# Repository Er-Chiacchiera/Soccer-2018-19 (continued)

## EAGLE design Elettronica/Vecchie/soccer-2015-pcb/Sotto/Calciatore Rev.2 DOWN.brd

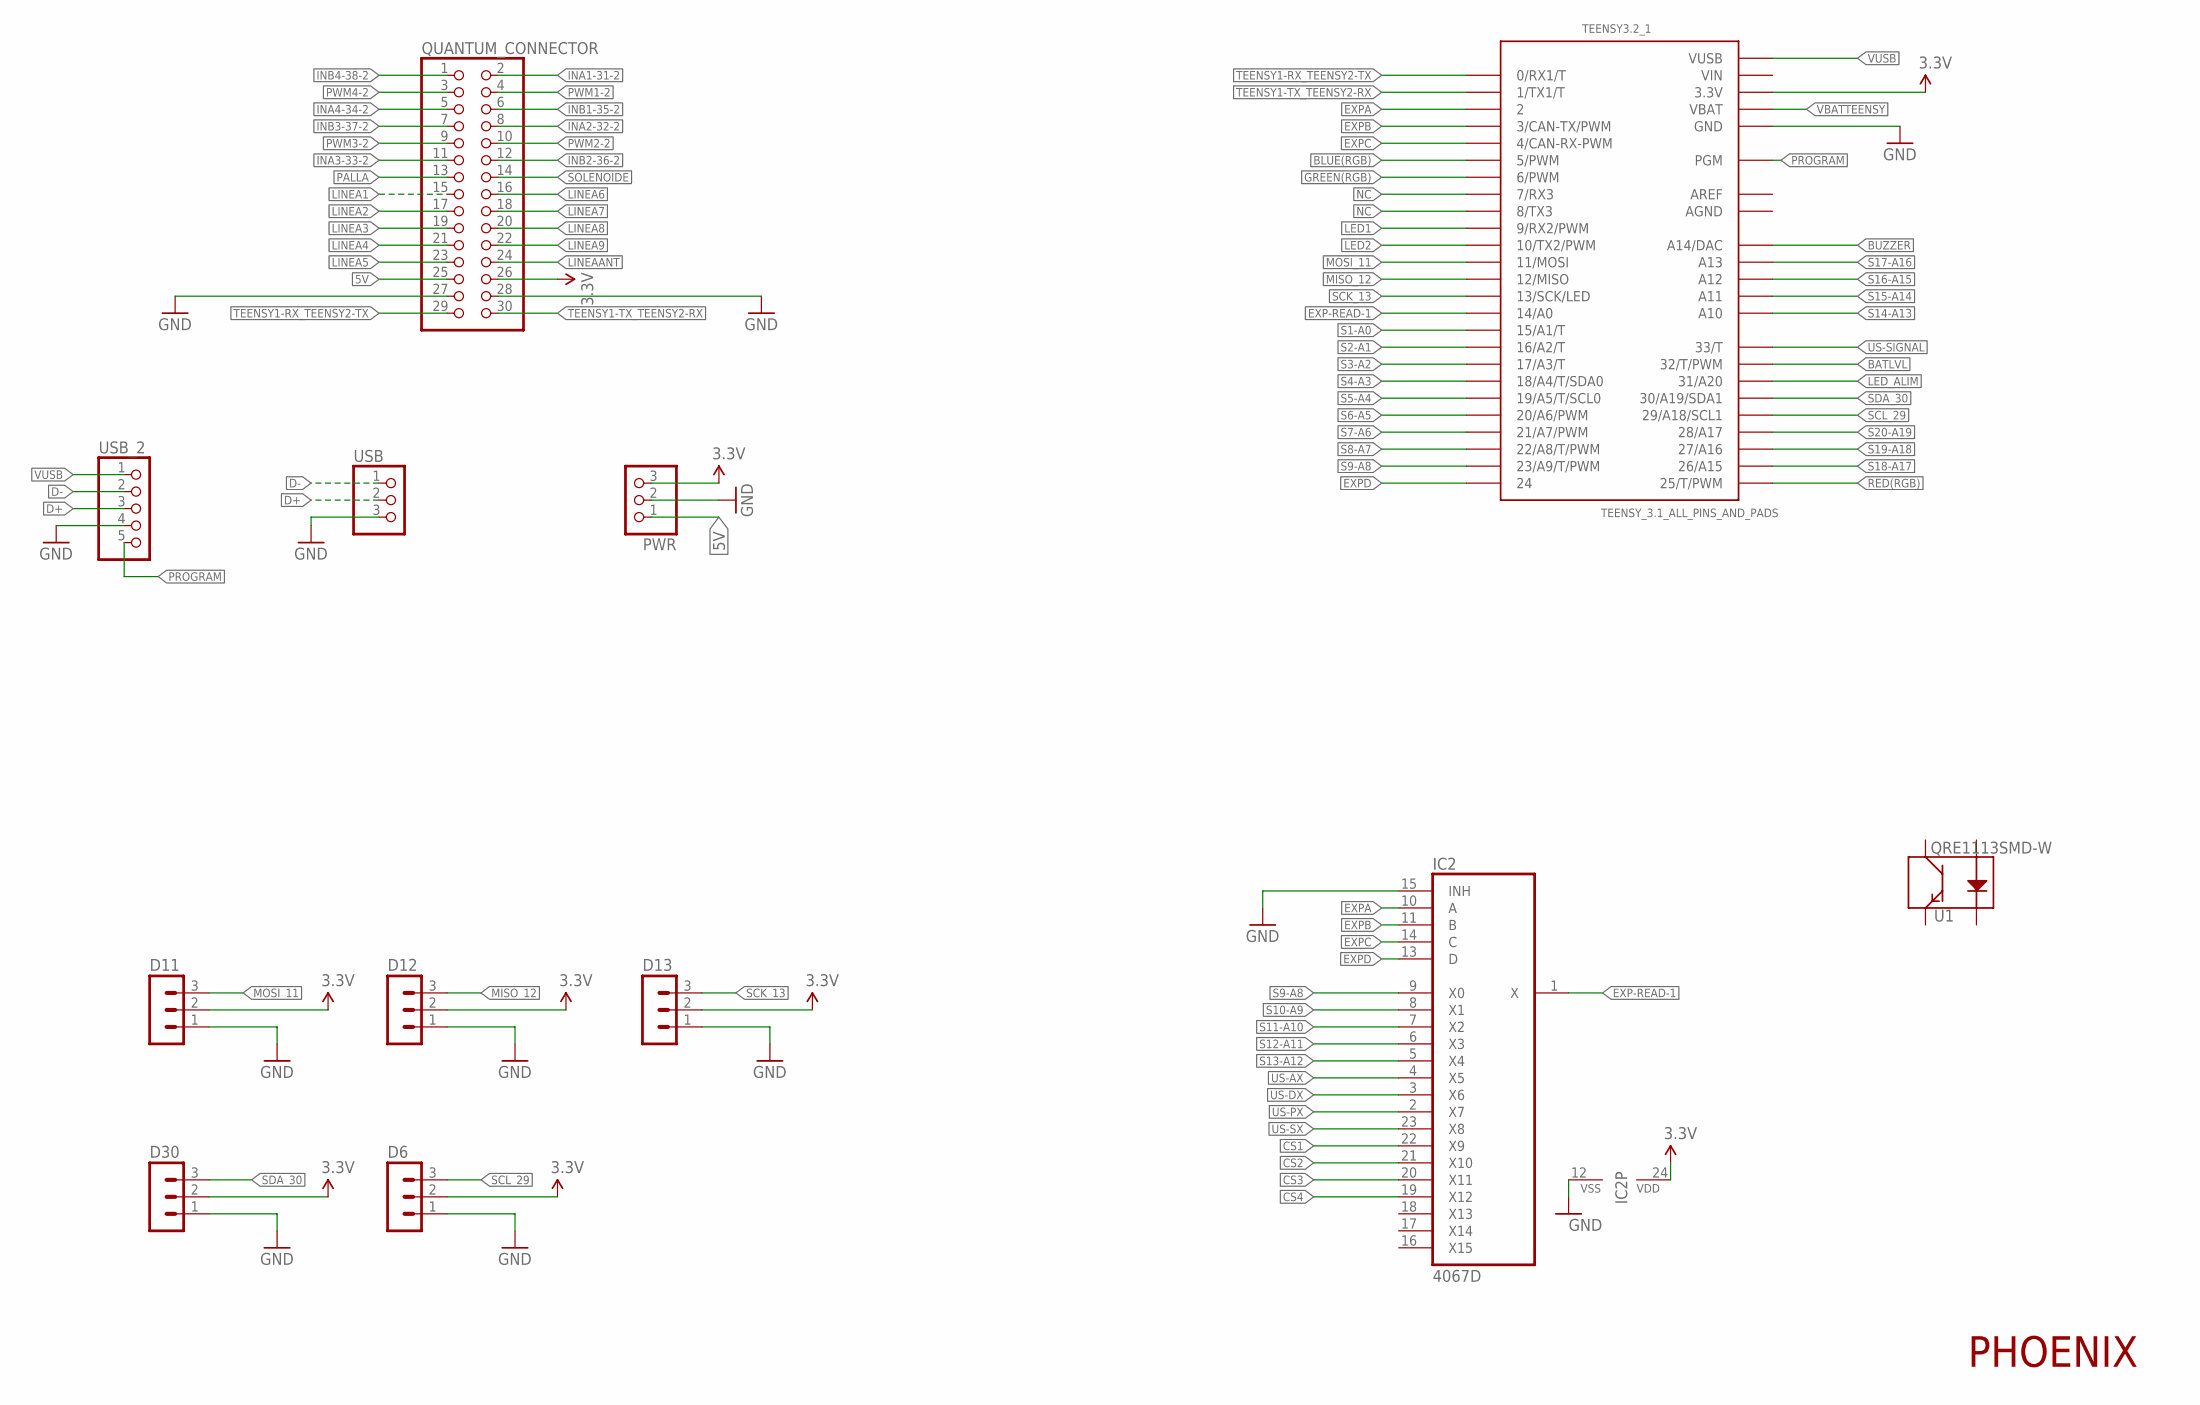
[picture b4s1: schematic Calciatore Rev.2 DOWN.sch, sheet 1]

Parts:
D6, D11, D12, D13, D30: MA03-1
IC2: 4067D; SO24W
PWR: PINHD-1X3; 1X03
QUANTUM_CONNECTOR: PINHD-2X15; 2X15
TEENSY3.2_1: TEENSY_3.1_ALL_PINS_AND_PADS; TEENSY3_ALL_PINS_&_PADS
U1: QRE1113SMD-W; QRE1113-W
USB: PINHD-1X3; 1X03
USB_2: PINHD-1X5; 1X05

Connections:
3.3V: D6.2, D11.2, D12.2, D13.2, D30.2, IC2.24 (VDD), PWR.3, QUANTUM_CONNECTOR.26, TEENSY3.2_1.3.3V, TEENSY3.2_1.3.3V1 (3.3V), TEENSY3.2_1.3.3V2 (3.3V); also elsewhere on the board
5V: PWR.1, QUANTUM_CONNECTOR.25; also elsewhere on the board
AGND: TEENSY3.2_1.AGND
AREF: TEENSY3.2_1.AREF
BATLVL: TEENSY3.2_1.32 (32/T/PWM); also elsewhere on the board
BLUE(RGB): TEENSY3.2_1.5 (5/PWM); also elsewhere on the board
BUZZER: TEENSY3.2_1.RESET/DAC (A14/DAC); also elsewhere on the board
CS1: IC2.22 (X9); also elsewhere on the board
CS2: IC2.21 (X10); also elsewhere on the board
CS3: IC2.20 (X11); also elsewhere on the board
CS4: IC2.19 (X12); also elsewhere on the board
D+: USB.2, USB_2.3
D-: USB.1, USB_2.2
EXP-READ-1: IC2.1 (X), TEENSY3.2_1.14/A0
EXPA: IC2.10 (A), TEENSY3.2_1.2
EXPB: IC2.11 (B), TEENSY3.2_1.3 (3/CAN-TX/PWM)
EXPC: IC2.14 (C), TEENSY3.2_1.4 (4/CAN-RX-PWM)
EXPD: IC2.13 (D), TEENSY3.2_1.24
GND: D6.1, D11.1, D12.1, D13.1, D30.1, IC2.12 (VSS), IC2.15 (INH), PWR.2, QUANTUM_CONNECTOR.27, QUANTUM_CONNECTOR.28, TEENSY3.2_1.GND, TEENSY3.2_1.GND1 (GND), TEENSY3.2_1.GND2 (GND), USB.3, USB_2.4; also elsewhere on the board
GREEN(RGB): TEENSY3.2_1.6 (6/PWM); also elsewhere on the board
INA1-31-2: QUANTUM_CONNECTOR.2; also elsewhere on the board
INA2-32-2: QUANTUM_CONNECTOR.8; also elsewhere on the board
INA3-33-2: QUANTUM_CONNECTOR.11; also elsewhere on the board
INA4-34-2: QUANTUM_CONNECTOR.5; also elsewhere on the board
INB1-35-2: QUANTUM_CONNECTOR.6; also elsewhere on the board
INB2-36-2: QUANTUM_CONNECTOR.12; also elsewhere on the board
INB3-37-2: QUANTUM_CONNECTOR.7; also elsewhere on the board
INB4-38-2: QUANTUM_CONNECTOR.1; also elsewhere on the board
LED1: TEENSY3.2_1.9 (9/RX2/PWM); also elsewhere on the board
LED2: TEENSY3.2_1.10 (10/TX2/PWM); also elsewhere on the board
LED_ALIM: TEENSY3.2_1.31 (31/A20); also elsewhere on the board
LINEA1: QUANTUM_CONNECTOR.15
LINEA2: QUANTUM_CONNECTOR.17
LINEA3: QUANTUM_CONNECTOR.19
LINEA4: QUANTUM_CONNECTOR.21
LINEA5: QUANTUM_CONNECTOR.23
LINEA6: QUANTUM_CONNECTOR.16
LINEA7: QUANTUM_CONNECTOR.18
LINEA8: QUANTUM_CONNECTOR.20
LINEA9: QUANTUM_CONNECTOR.22
LINEAANT: QUANTUM_CONNECTOR.24
MISO_12: D12.3, TEENSY3.2_1.12 (12/MISO)
MOSI_11: D11.3, TEENSY3.2_1.11 (11/MOSI)
NC: TEENSY3.2_1.7 (7/RX3), TEENSY3.2_1.8 (8/TX3)
PALLA: QUANTUM_CONNECTOR.13
PROGRAM: TEENSY3.2_1.PGM, USB_2.5
PWM1-2: QUANTUM_CONNECTOR.4; also elsewhere on the board
PWM2-2: QUANTUM_CONNECTOR.10; also elsewhere on the board
PWM3-2: QUANTUM_CONNECTOR.9; also elsewhere on the board
PWM4-2: QUANTUM_CONNECTOR.3; also elsewhere on the board
RED(RGB): TEENSY3.2_1.25 (25/T/PWM); also elsewhere on the board
S1-A0: TEENSY3.2_1.15/A1 (15/A1/T); also elsewhere on the board
S2-A1: TEENSY3.2_1.16/A2 (16/A2/T); also elsewhere on the board
S3-A2: TEENSY3.2_1.17/A3 (17/A3/T); also elsewhere on the board
S4-A3: TEENSY3.2_1.18/A4 (18/A4/T/SDA0); also elsewhere on the board
S5-A4: TEENSY3.2_1.19/A5 (19/A5/T/SCL0); also elsewhere on the board
S6-A5: TEENSY3.2_1.20/A6 (20/A6/PWM); also elsewhere on the board
S7-A6: TEENSY3.2_1.21/A7 (21/A7/PWM); also elsewhere on the board
S8-A7: TEENSY3.2_1.22/A8 (22/A8/T/PWM); also elsewhere on the board
S9-A8: IC2.9 (X0), TEENSY3.2_1.23/A9 (23/A9/T/PWM); also elsewhere on the board
S10-A9: IC2.8 (X1); also elsewhere on the board
S11-A10: IC2.7 (X2); also elsewhere on the board
S12-A11: IC2.6 (X3); also elsewhere on the board
S13-A12: IC2.5 (X4); also elsewhere on the board
S14-A13: TEENSY3.2_1.A10; also elsewhere on the board
S15-A14: TEENSY3.2_1.A11; also elsewhere on the board
S16-A15: TEENSY3.2_1.A12; also elsewhere on the board
S17-A16: TEENSY3.2_1.A13; also elsewhere on the board
S18-A17: TEENSY3.2_1.26 (26/A15); also elsewhere on the board
S19-A18: TEENSY3.2_1.27 (27/A16); also elsewhere on the board
S20-A19: TEENSY3.2_1.28 (28/A17); also elsewhere on the board
SCK_13: D13.3, TEENSY3.2_1.13 (13/SCK/LED)
SCL_29: D6.3, TEENSY3.2_1.29 (29/A18/SCL1)
SDA_30: D30.3, TEENSY3.2_1.30 (30/A19/SDA1)
SOLENOIDE: QUANTUM_CONNECTOR.14; also elsewhere on the board
TEENSY1-RX_TEENSY2-TX: QUANTUM_CONNECTOR.29, TEENSY3.2_1.0 (0/RX1/T)
TEENSY1-TX_TEENSY2-RX: QUANTUM_CONNECTOR.30, TEENSY3.2_1.1 (1/TX1/T)
US-AX: IC2.4 (X5); also elsewhere on the board
US-DX: IC2.3 (X6); also elsewhere on the board
US-PX: IC2.2 (X7); also elsewhere on the board
US-SIGNAL: TEENSY3.2_1.33 (33/T); also elsewhere on the board
US-SX: IC2.23 (X8); also elsewhere on the board
VBATTEENSY: TEENSY3.2_1.VBAT
VIN: TEENSY3.2_1.VIN; also elsewhere on the board
VUSB: TEENSY3.2_1.VUSB, USB_2.1

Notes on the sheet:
PHOENIX

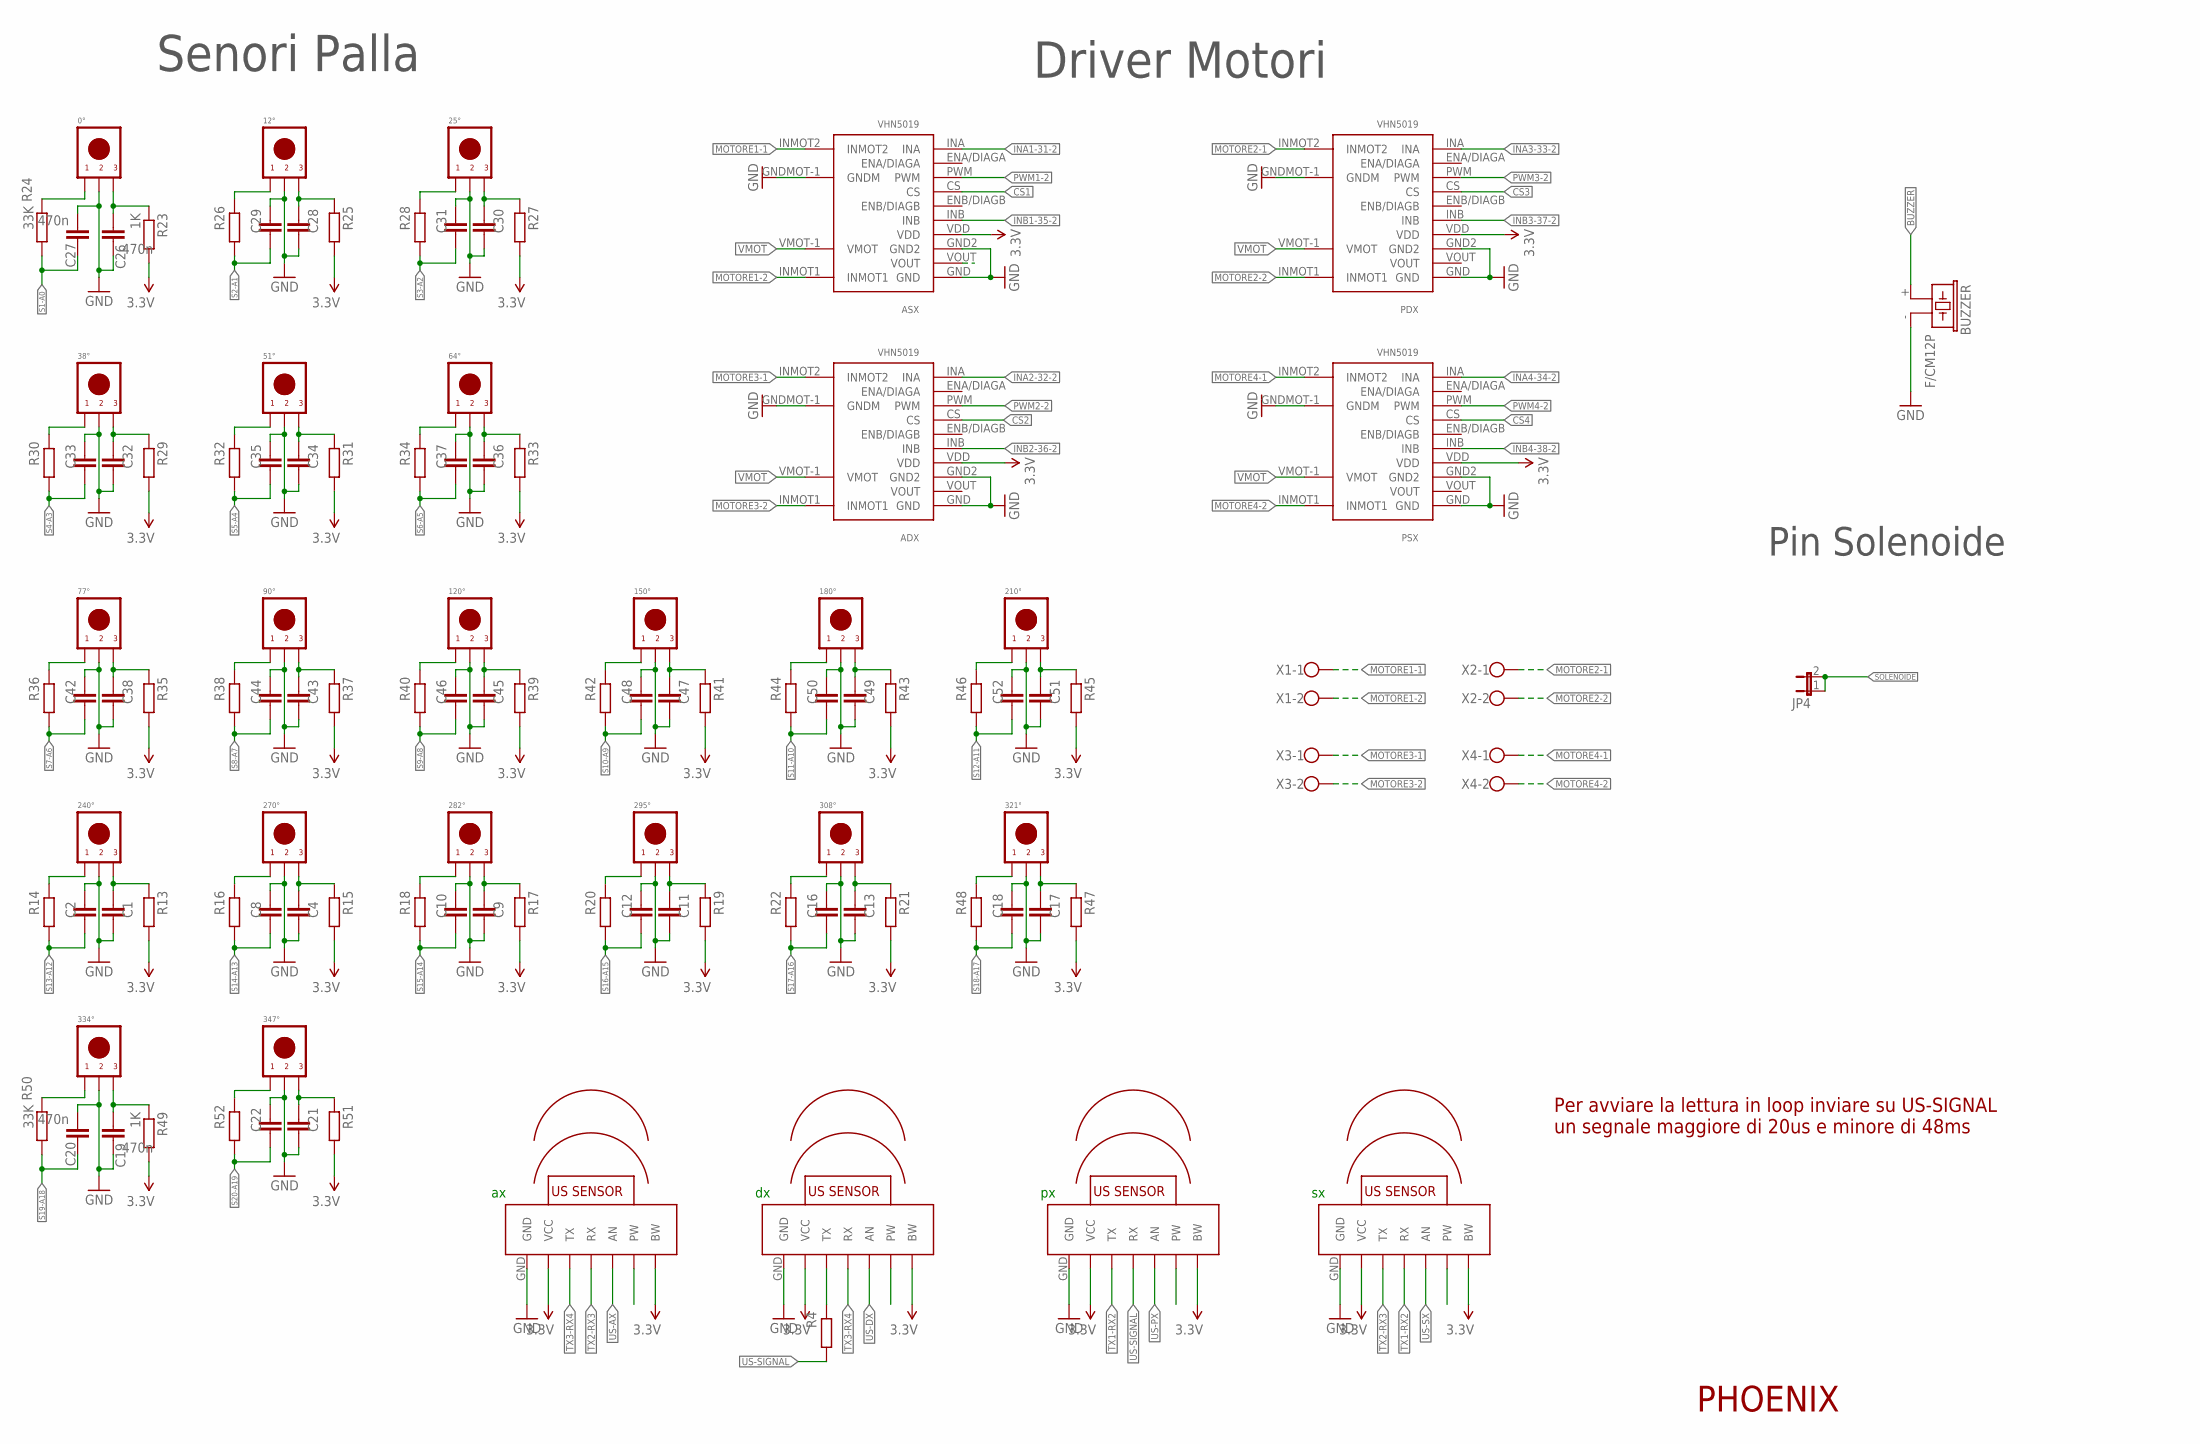
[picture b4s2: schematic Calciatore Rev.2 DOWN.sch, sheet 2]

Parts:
0°, 12°, 25°, 38°, 51°, 64°, 77°, 90°, 120°, 150°, 180°, 210°, 240°, 270°, 282°, 295°, 308°, 321°, 334°, 347°: effe; TSOP4840
ADX: VHN5019; MOTOR-SHIELD
ASX: VHN5019; MOTOR-SHIELD
AX: MB1010
BUZZER: F/CM12P
C1, C2, C4, C8, C9, C10, C11, C12, C13, C16, C17, C18, C21, C22, C28, C29, C30, C31, C32, C33, C34, C35, C36, C37, C38, C42, C43, C44, C45, C46, C47, C48, C49, C50, C51, C52: C-EUC1206; C1206
C19, C20, C26, C27: 470n; C1206
DX: MB1010
JP4: JP1E; JP1
PDX: VHN5019; MOTOR-SHIELD
PSX: VHN5019; MOTOR-SHIELD
PX: MB1010
R4, R13, R14, R15, R16, R17, R18, R19, R20, R21, R22, R25, R26, R27, R28, R29, R30, R31, R32, R33, R34, R35, R36, R37, R38, R39, R40, R41, R42, R43, R44, R45, R46, R47, R48, R51, R52: R-EU_M1206; M1206
R23, R49: 1K; M1206
R24, R50: 33K; M1206
SX: MB1010
X1, X2, X3, X4: W237-102

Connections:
3.3V: ADX.VDD, ASX.VDD, AX.BW, AX.VCC, DX.BW, DX.VCC, PDX.VDD, PSX.VDD, PX.BW, PX.VCC, R13.2, R15.2, R17.2, R19.2, R21.2, R23.2, R25.2, R27.2, R29.2, R31.2, R33.2, R35.2, R37.2, R39.2, R41.2, R43.2, R45.2, R47.2, R49.2, R51.2, SX.BW, SX.VCC; also elsewhere on the board
BUZZER: BUZZER.+ (1); also elsewhere on the board
CS1: ASX.CS; also elsewhere on the board
CS2: ADX.CS; also elsewhere on the board
CS3: PDX.CS; also elsewhere on the board
CS4: PSX.CS; also elsewhere on the board
GND: 0°.GND, 12°.GND, 25°.GND, 38°.GND, 51°.GND, 64°.GND, 77°.GND, 90°.GND, 120°.GND, 150°.GND, 180°.GND, 210°.GND, 240°.GND, 270°.GND, 282°.GND, 295°.GND, 308°.GND, 321°.GND, 334°.GND, 347°.GND, ADX.GND, ADX.GND2, ADX.GNDMOT-1 (GNDM), ASX.GND, ASX.GND2, ASX.GNDMOT-1 (GNDM), AX.GND, BUZZER.- (2), C1.2, C2.1, C4.2, C8.1, C9.2, C10.1, C11.2, C12.1, C13.2, C16.1, C17.2, C18.1, C19.2, C20.2, C21.2, C22.1, C26.2, C27.2, C28.2, C29.1, C30.2, C31.1, C32.2, C33.1, C34.2, C35.1, C36.2, C37.1, C38.2, C42.1, C43.2, C44.1, C45.2, C46.1, C47.2, C48.1, C49.2, C50.1, C51.2, C52.1, DX.GND, PDX.GND, PDX.GND2, PDX.GNDMOT-1 (GNDM), PSX.GND, PSX.GND2, PSX.GNDMOT-1 (GNDM), PX.GND, SX.GND; also elsewhere on the board
INA1-31-2: ASX.INA; also elsewhere on the board
INA2-32-2: ADX.INA; also elsewhere on the board
INA3-33-2: PDX.INA; also elsewhere on the board
INA4-34-2: PSX.INA; also elsewhere on the board
INB1-35-2: ASX.INB; also elsewhere on the board
INB2-36-2: ADX.INB; also elsewhere on the board
INB3-37-2: PDX.INB; also elsewhere on the board
INB4-38-2: PSX.INB; also elsewhere on the board
MOTORE1-1: ASX.INMOT2, X1.1
MOTORE1-2: ASX.INMOT1, X1.2
MOTORE2-1: PDX.INMOT2, X2.1
MOTORE2-2: PDX.INMOT1, X2.2
MOTORE3-1: ADX.INMOT2, X3.1
MOTORE3-2: ADX.INMOT1, X3.2
MOTORE4-1: PSX.INMOT2, X4.1
MOTORE4-2: PSX.INMOT1, X4.2
unnamed: 0°.VCC, C26.1, R23.1
unnamed: 0°.OUT, R24.1
unnamed: 12°.VCC, C28.1, R25.1
unnamed: 12°.OUT, R26.1
unnamed: 240°.VCC, C1.1, R13.1
unnamed: 270°.VCC, C4.1, R15.1
unnamed: 282°.VCC, C9.1, R17.1
unnamed: 25°.OUT, R28.1
unnamed: 38°.OUT, R30.1
unnamed: 51°.OUT, R32.1
unnamed: 25°.VCC, C30.1, R27.1
unnamed: 295°.VCC, C11.1, R19.1
unnamed: 308°.VCC, C13.1, R21.1
unnamed: 321°.VCC, C17.1, R47.1
unnamed: 64°.OUT, R34.1
unnamed: 38°.VCC, C32.1, R29.1
unnamed: 77°.OUT, R36.1
unnamed: 51°.VCC, C34.1, R31.1
unnamed: 120°.OUT, R40.1
unnamed: 64°.VCC, C36.1, R33.1
unnamed: 180°.OUT, R44.1
unnamed: 77°.VCC, C38.1, R35.1
unnamed: 90°.OUT, R38.1
unnamed: 90°.VCC, C43.1, R37.1
unnamed: 150°.OUT, R42.1
unnamed: 120°.VCC, C45.1, R39.1
unnamed: 210°.OUT, R46.1
unnamed: 150°.VCC, C47.1, R41.1
unnamed: 240°.OUT, R14.1
unnamed: 180°.VCC, C49.1, R43.1
unnamed: 270°.OUT, R16.1
unnamed: 210°.VCC, C51.1, R45.1
unnamed: 282°.OUT, R18.1
unnamed: 295°.OUT, R20.1
unnamed: 308°.OUT, R22.1
unnamed: 321°.OUT, R48.1
unnamed: 334°.VCC, C19.1, R49.1
unnamed: 347°.VCC, C21.1, R51.1
unnamed: 334°.OUT, R50.1
unnamed: 347°.OUT, R52.1
unnamed: DX.TX, R4.1
PWM1-2: ASX.PWM; also elsewhere on the board
PWM2-2: ADX.PWM; also elsewhere on the board
PWM3-2: PDX.PWM; also elsewhere on the board
PWM4-2: PSX.PWM; also elsewhere on the board
S1-A0: C27.1, R24.2; also elsewhere on the board
S2-A1: C29.2, R26.2; also elsewhere on the board
S3-A2: C31.2, R28.2; also elsewhere on the board
S4-A3: C33.2, R30.2; also elsewhere on the board
S5-A4: C35.2, R32.2; also elsewhere on the board
S6-A5: C37.2, R34.2; also elsewhere on the board
S7-A6: C42.2, R36.2; also elsewhere on the board
S8-A7: C44.2, R38.2; also elsewhere on the board
S9-A8: C46.2, R40.2; also elsewhere on the board
S10-A9: C48.2, R42.2; also elsewhere on the board
S11-A10: C50.2, R44.2; also elsewhere on the board
S12-A11: C52.2, R46.2; also elsewhere on the board
S13-A12: C2.2, R14.2; also elsewhere on the board
S14-A13: C8.2, R16.2; also elsewhere on the board
S15-A14: C10.2, R18.2; also elsewhere on the board
S16-A15: C12.2, R20.2; also elsewhere on the board
S17-A16: C16.2, R22.2; also elsewhere on the board
S18-A17: C18.2, R48.2; also elsewhere on the board
S19-A18: C20.1, R50.2; also elsewhere on the board
S20-A19: C22.2, R52.2; also elsewhere on the board
SOLENOIDE: JP4.1, JP4.2; also elsewhere on the board
TX1-RX2: PX.TX, SX.RX
TX2-RX3: AX.RX, SX.TX
TX3-RX4: AX.TX, DX.RX
US-AX: AX.AN; also elsewhere on the board
US-DX: DX.AN; also elsewhere on the board
US-PX: PX.AN; also elsewhere on the board
US-SIGNAL: PX.RX, R4.2; also elsewhere on the board
US-SX: SX.AN; also elsewhere on the board
VMOT: ADX.VMOT-1 (VMOT), ASX.VMOT-1 (VMOT), PDX.VMOT-1 (VMOT), PSX.VMOT-1 (VMOT); also elsewhere on the board
VOUT: ASX.VOUT

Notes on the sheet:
Driver Motori
Senori Palla
Pin Solenoide
PHOENIX
Per avviare la lettura in loop inviare su US-SIGNAL un segnale maggiore di 20us e minore di 48ms

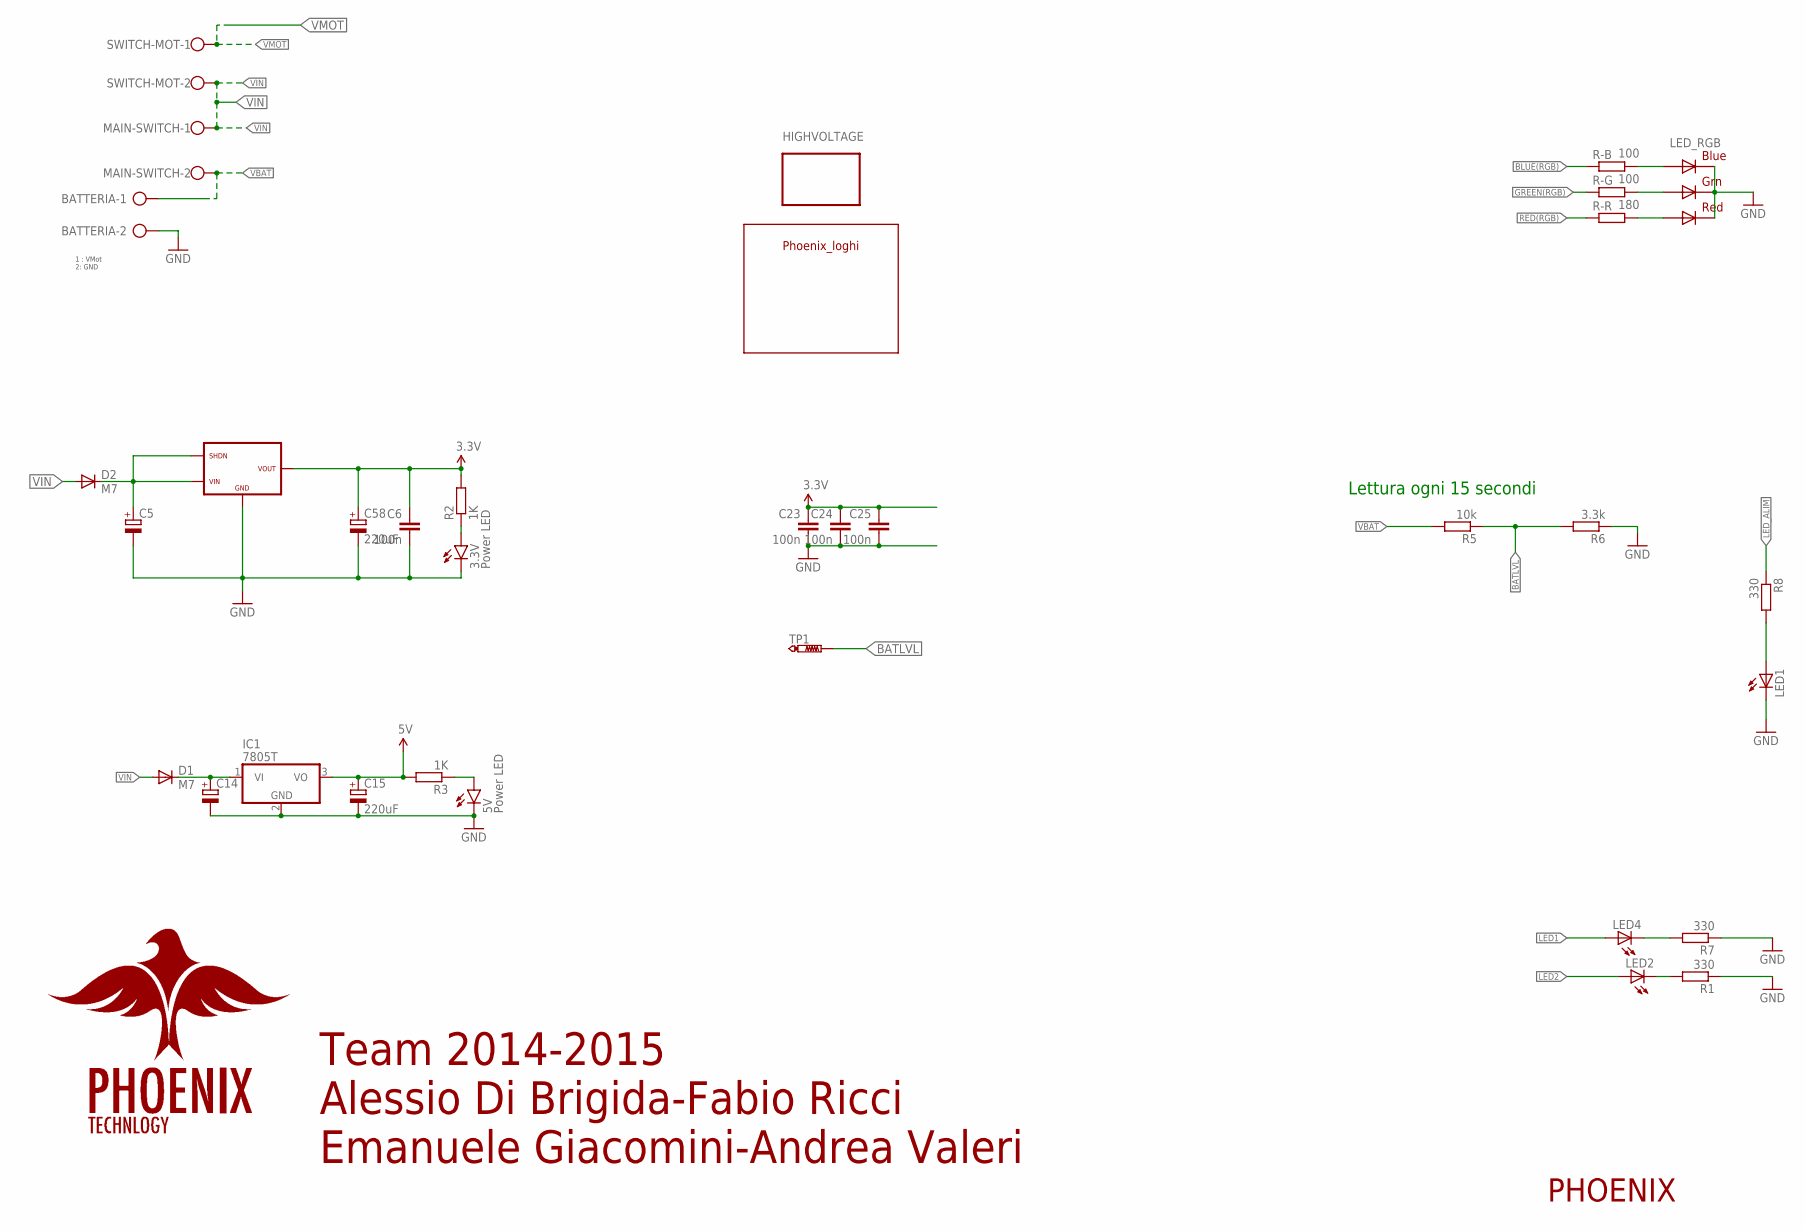
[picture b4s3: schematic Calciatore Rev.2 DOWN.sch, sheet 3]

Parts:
3.3V, 5V: Power LED; FKIT-LED-1206
BATTERIA: AK500/2-H
C5, C14: CPOL-EUE5-8.5; E5-8,5
C6, C23, C24, C25: 100n; C1206
C15, C58: 220uF; E5-8,5
D1, D2: M7; SMB
HIGHVOLTAGE: LOGO; LOGOHV
IC1: 7805T; TO220H
LED1, LED2, LED4: LEDSMT1206; 1206
LED_RGB: RGBLED5050
MAIN-SWITCH: W237-102
R1, R7, R8: 330; M1206
R2, R3: 1K; M1206
R5: 10k; M1206
R6: 3.3k; M1206
R-B: 100; M1206
R-G: 100; M1206
R-R: 180; M1206
SWITCH-MOT: W237-102
TP1: PTR1TP17SQ; TP17SQ
U$8: PHOENIX_LOGHI
U$10: ALIM; ALIM_SWITCHING

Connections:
3.3V: C6.1, C23.1, C24.1, C25.1, C58.+, R2.2, U$10.VOUT; also elsewhere on the board
5V: C15.+, IC1.3 (VO), R3.2; also elsewhere on the board
BATLVL: R5.1, R6.2, TP1.TP; also elsewhere on the board
BLUE(RGB): R-B.1; also elsewhere on the board
GND: 3.3V.C, 5V.C, BATTERIA.2, C5.-, C6.2, C14.-, C15.-, C23.2, C24.2, C25.2, C58.-, IC1.2 (GND), LED1.C, LED_RGB.4 (BLUE_C), LED_RGB.5 (RED_C), LED_RGB.6 (GREEN_C), R1.1, R6.1, R7.1, U$10.GND; also elsewhere on the board
GREEN(RGB): R-G.1; also elsewhere on the board
LED1: LED4.A; also elsewhere on the board
LED2: LED2.A; also elsewhere on the board
LED_ALIM: R8.1; also elsewhere on the board
unnamed: LED2.C, R1.2
unnamed: LED1.A, R8.2
unnamed: C5.+, D2.C, U$10.SHDN, U$10.VIN
unnamed: 3.3V.A, R2.1
unnamed: LED_RGB.3 (BLUE_A), R-B.2
unnamed: LED_RGB.1 (GREEN_A), R-G.2
unnamed: LED4.C, R7.2
unnamed: LED_RGB.2 (RED_A), R-R.2
unnamed: C14.+, D1.C, IC1.1 (VI)
unnamed: 5V.A, R3.1
RED(RGB): R-R.1; also elsewhere on the board
VBAT: BATTERIA.1, MAIN-SWITCH.2, R5.2
VIN: D1.A, D2.A, MAIN-SWITCH.1, SWITCH-MOT.2; also elsewhere on the board
VMOT: SWITCH-MOT.1; also elsewhere on the board

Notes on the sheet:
Team 2014-2015 Alessio Di Brigida-Fabio Ricci Emanuele Giacomini-Andrea Valeri
PHOENIX
1 : VMot 2: GND
Lettura ogni 15 secondi

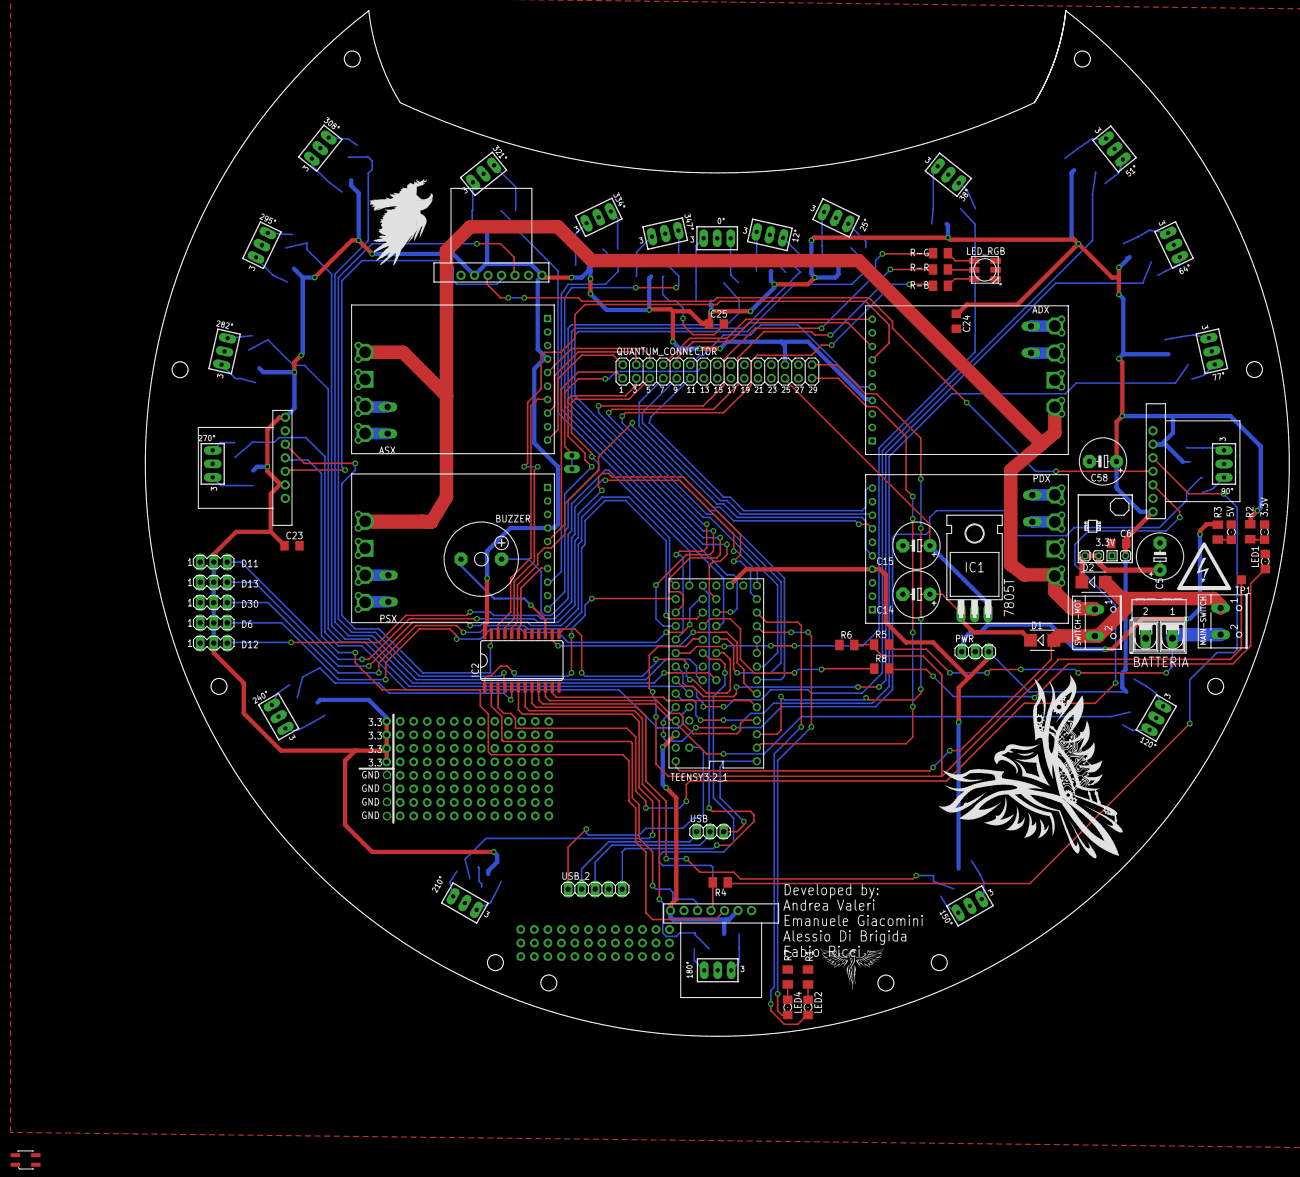
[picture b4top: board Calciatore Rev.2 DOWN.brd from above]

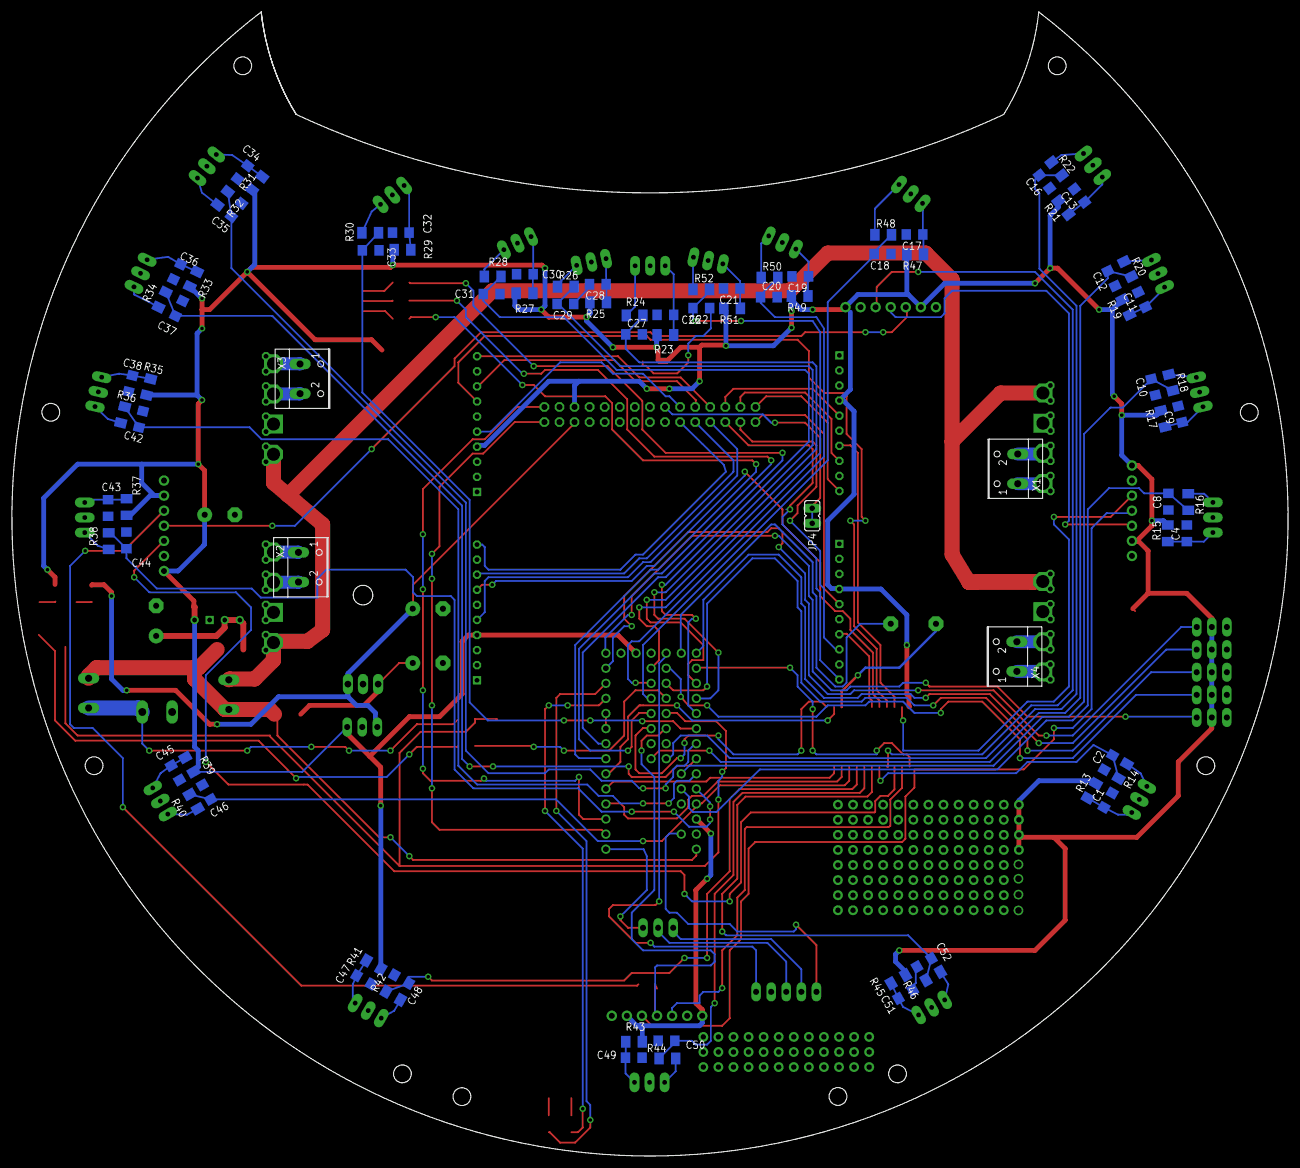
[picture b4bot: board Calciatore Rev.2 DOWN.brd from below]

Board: 2 copper layers, 215.0 x 192.7 mm, 163 parts (85 on the bottom side), 135 nets.

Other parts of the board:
U$5: EAGLE-PLC-12MM
U$12: PHOENIX

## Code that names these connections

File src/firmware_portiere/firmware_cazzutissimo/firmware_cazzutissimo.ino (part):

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


int led1 = 8;
int led2 = 33;
int led3 = 9;  //alto a destra
int led4 = 12;  //per calibrazione
int led5 = 10;  //NON FUNZICA
int led6 = 35; //basso a sinistra
int led7 = A7;  //centrale
int led8 = 37;  //alto a sinistra
int encoder_sel = 40;
int batteria = A2;
int solenoid = 43;

void setup() {
  
  pinMode(led1, OUTPUT);
  pinMode(led2, OUTPUT);
  pinMode(led3, OUTPUT);
  pinMode(led4, OUTPUT);
  pinMode(led8, OUTPUT);
  pinMode(led7, OUTPUT);
  pinMode(batteria, INPUT);
  pinMode(solenoid, OUTPUT);
  Serial.begin(9600);
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
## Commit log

2019-03-06 new_repo
2019-03-06 repo_ready
2019-03-06 Src_delete
2019-03-06 modifiche a bussola maniglie e pixy
2019-03-06 Aggiunta cartella src
2019-03-06 Pulizia
2019-03-06 modifiche a pt13
2019-03-06 Src nuova con bussola
2019-03-06 Prova da terminale
2019-03-06 Delete_prova_terminaleMACOS
2019-03-07 Modifiche per linee
2019-03-07 lineee
2019-03-07 Prova per connessioni motori
2019-03-08 connessioni
2019-03-08 PICCOLE SISTEMAZIONI
2019-03-08 motori + imu
2019-03-10 sistemati buchi delle basi e creato supporto pixy2
2019-03-10 file per encoder
2019-03-11 piccoli aggiustamenti
2019-03-11 src_encoder
2019-03-12 src con encoder
2019-03-12 src, aggiunti test di simulazione
2019-03-13 Test_src
2019-03-13 sistemato supporto pixy e rampa
2019-03-14 Src per jack
2019-03-14 src per jack2
2019-03-14 Update ADS1015 issues
2019-03-14 Fix ADS1015 Issues
2019-03-14 Aggiunta I2C scanner
2019-03-15 src_SENSORI_DI_LINEA
2019-03-17 src con Eeprom
2019-03-18 spena non rompere
    moifiche a ruote
2019-03-21 src per pixy2
2019-03-21 pixy
2019-03-21 fix pixy
2019-03-21 Start final program
2019-03-22 aggiunta porta
2019-03-22 src con pixy
2019-03-25 Src + connection
2019-04-15 aggiunta libreria di Gestione
2019-04-16 aggiunta libreria per gestione e modifiche
2019-04-16 modifiche sul globals
2019-04-19 src change
2019-04-26 per jack
2019-04-28 Austria
2019-04-30 modifiche firmware
2019-04-30 modifiche di cartelle ecc.
2019-05-02 implemento ultrasuoni
2019-05-03 modifiche ultrasuoni
2019-05-04 ultrasuoni e commenti
2019-05-09 pusho tutto qua
2019-05-10 fix_merge
2019-05-10 fix_delete_firmware
2019-05-10 modifiche minime
2019-05-13 modifiche cartelle
2019-05-13 sviluppo encoder e PID per ogni motore
2019-05-14 prime modifiche e prove con encoder
2019-05-14 Cambiamenti al 3d
    paratia pixy ruote tappi e supporto batteria
2019-05-16 modifiche software per encoder
2019-05-16 speed -> new_speed
    cambio di variabili da speed a new_speed per problemi di lettura da parte del compilatore arduino
2019-05-22 delete
2019-05-26 comment
2019-06-06 Bumper
2019-06-20 ciao
2019-06-22 aggiornamenti gara
2019-06-22 for encoders
2019-06-22 migliorati sistemi di calbrazione
2019-06-30 PCB schematico
2019-06-30 Sens linea schematico
2019-11-21 2019/20 src
2020-01-30 Elettronica modifiche
